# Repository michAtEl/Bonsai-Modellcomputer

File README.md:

# Bonsai-Modellcomputer
Der Bonsai-Modellcomputer wurde von Klaus Merkert für den Einsatz im Informatikunterricht entwickelt. Auf folgender Seite findet man unter anderem Schaltpläne und Platinenlayouts von Klaus Merkert zum Bau eines Bonsai-Modellcomputers:
http://www.hsg-kl.de/faecher/inf/material/bonsai/

Es gibt auch eine Simulation des Lerncomputers (https://bonsai.pinyto.de/), die im digitalen Informatik-Schulbuch http://inf-schule.de verwendet wird.

Viele Bauteile, die in den Plänen von Klaus Merkert verwendet werden, wurden abgekündigt und sind heue (Stand 2021) nicht mehr verfügbar.
Ziel dieses Projektes ist es deshalb, eine Version des Bonsai-Modellcomputer zu entwickeln, die möglichst leicht nachgebaut werden kann.

# Projekstatus
Der Prototyp funktioniert und wurde im Unterricht eingesetzt. In den Github-Issues sind einige kleinere Probleme beschrieben, die vor einem weiteren Nachbau behoben werden könnten.

# Änderungen gegenüber den Plänen von Klaus Merkert
- Die Namen und Reihenfolge der Steuersignale wurden an den Simulator angepasst (vgl. https://bonsai.pinyto.de/documentation/micro/)
- Alle Schaltpläne und Platinen wurden mit der Software KiCad gezeichnet (http://kicad.org).
- Für die Platinen wurden neue Layouts entwickelt, damit die Möglichkeiten eines doppelseitigen Layouts besser genutzt werden können.
- Die Steckverbinder zur Verbindung der Steuersignale sowie der Spannungsversorgung mit den Platinen wurden ersetzt durch Reichelt PSK (Alternativ kann man Molex KK verwenden. Diese Steckverbinder sind besser, aber auch deutlich teurer).
- Alle Bauteile der Familie 74LS wurden durch Bauteile der Familien 74HC oder 74HCT ersetzt.
- Zur Nullentdeckung auf der Platine Befehle wurde eine Wired-And-Verknüpfung mit Open-Collector-Ausgängen verwendet. Diese Wired-And-Verknüpfung wurde durch Gatter in einem 74HC08 ersetzt.
- Zur Erzeugung eines automatischen Taktsignals wird ein Mikrocontroller (Atmega 48-20P) verwendet. Der Quellcode liegt im Verzeichnis EinTaktReset-src. Der Quellcode kann mit dem Microchip Studio compiliert werden. Der Mikrocontroller kann anschließend über den ISP-Header auf der Platine EinTaktReset programmiert werden.

# Eine Bonsai nachbauen
## Beschaffung der Bauteile
- Flachbandkabel: Diese Flachbandkabel kann man aus IDE-Kabeln herstellen.
- Taster Digitast: Diese Schalter sind in den letzten Jahren sehr teuer geworden (ca. 5€ pro Taster). Kompatible Nachbauten findet man auf der Seite https://de.aliexpress.com/ unter der Bezeichnung PB86. Zur Sicherheit: Datenblatt (insbesondere Abmessungen und interne Schaltung) prüfen!
- Die Steckverbinder 

## Platinen fertigen lassen
Die Pläne wurden mit KiCad gezeichnet. In den *.kicad_sch-Dateien befinden sich die Schaltpläne, die Platinenlayouts sind in den *.kicad_pcb-Dateien. Um die Platinen fertigen zu lassen, muss man das Platinenlayout in ein Format exportieren, dass der Hersteller versteht. In der Regel ist das Gerber. Die Gerber-Exporte, die bei dem Prototypen verwendet wurden, liegen im Verzeichnis gerber. Diese Gerber-Dateien wurden von https://jlcpcb.com/ problemlos gefertigt.

## Platinen bestücken
Es werden nur bedrahtete Bauteile (keine SMD-Bauteile) verwendet, da bedrahtete Bauteile von Lötanfängern (z.B. Schülern) leichter bestückt werden können. Es ist sinnvoll, bei allen ICs je einen Sockel zu verwenden.

Der Bestückungsdruck der Platinen wird für Hinweise zur Bedienung des Rechners verwendet.
Die Bezeichnungen der Bauteile stehen nicht im Bestückungsdruck.
Man erfährt diese Bezeichnungen, indem man das KiCad-Projekt zu der Platinen, an der man gerade arbeitet, betrachtet. Dazu öffnet man zunächst die Projektdatei (.kicad_pro). Aus der Kicad-Projektansicht kann man dann den Schaltplan und das Board mit einem Doppelclick öffnen. Wenn man die Dateien so öffnet, sind Schaltplan und Board verknüpft. D.h.: Klickt man im Schaltplan / Board auf ein Bauteil, so wird dieses Bauteil automatisch auch im Bard / Schaltplan hervorgehoben. So versteht man leichter, welche Aufgabe ein bestimmtes Bauteil auf dem Board hat. 

Es empfiehlt sich, die Platinen in der folgenden Reihenfolge zu bestücken:
- Spanngsversorgung (KiCad-Projekt power-schmal). Diese Platine wird später benötigt, um andere Platinen zu testen.
- Akku und PC. Diese Platinen können einzeln getestet werden. Achtung: Die Platinen sind gleich, sie unterscheiden sich jedoch in der Farbe der LEDs und den Widerständen R2 und R2 (vgl. Schaltplan sowie [Bonsai.jpg](Bonsai.jpg))
- Speicher
- Ein/Takt/Reset. Nun können alle bisher gebauten Platinen gemeinsam getestet werden. Man verkabelt die Platinen. Dann kann man mit den Kippschaltern Zahlen eingeben, diese Zahlen speichern und anschließend wider auf den Datenbus schreiben.
- restliche Platinen

## Platine Ein/Takt/Reset
Von dieser Platine gibt es eine neue Version. Im Bild [Bonsai.jpg](Bonsai.jpg) ist noch die alte Version abgebildet. In der neuen Version wird der Takt von einem Mikrocontroller (ATmega48) erzeugt. Dieser Controller muss programmiert werden. Die Programmierung kann direkt in der Schaltung mit Hilfe der 6-poligen Pinleiste erfolgen. Man benötigt dazu einen ISP-Adapter für ATmega-Controller. Der Quellcode befindet sich im Ordner EinTaktReset-src.

## Platinen verdrahten
Bei der Verdrahtung kann man sich orientieren
- [am Bild des Computers](Bonsai.jpg)
- [Verdrahtung](Verdrahtung.svg) Tipp: Datei in Inkscape öffnen; die Datei ist im Maßstab 1:1 gezeichnet
- an der Verdrahtungsanleitung von Klaus Merkert (https://www.hsg-kl.de/faecher/inf/material/bonsai/bau/verdraht/index.php)

Crimpanleitung für die Steckverbinder Reichelt PSK: https://www.reichelt.de/reicheltpedia/index.php/Crimp_Anleitungen#Crimpen_von_PSK-Kontakten

Als Flachbandkabel kann man alte IDE-Kabel verwenden. Mann muss jedoch einige Leitungen abtrennen und neue Stecker crimpen.

Die Kabelhalter können mit einem 3D-Drucker gedruckt werden. Eine OpenSCAD-Datei befindet sich im Ordner Kabelhalter: [Kabelhalter.scad](Kabelhalter/Kabelhalter.scad)

## Spannungsversorgung
Der Bonsai läuft mit einer Gleichspannung von 5V. Es mehrere Möglichkeiten, wie man diese Spannung bereitstellen kann:

- Man verwendet ein Festspannungsnetzteil, das 5V ausgibt. Aus Lochrasterplatinenmaterial baut man eine Platine, auf der sich eine Buchse für das Netzteil sowie sechs 2-polige Steckerleisten für 2-polige PSK-Stecker befinden (pro Platine eine Steckerleiste).
- Man baut eine kleine Platine mit einem Festspannungsregler (7805). Dazu kann man z.B. die Platine im Ordner power-schmal verwenden. Diese Platine benötigt eine Eingangsspannung, die irgendwo zwischen ca. 7V und ca. 15V liegen sollte. Dazu kann man z.B. ein Labornetzgerät verwenden.  Das Labornetzgerät hat gegenüber einem Steckernetzteil den Vorteil, dass man die Stromstärke an dem Netzteil ablesen kann und so eine kontrolle hat, ob der Bonsai richtig funktioniert. Bei dem vollständigen Bonsai liegt die Stromstärke (je nach dem, wie viele LEDs gerade leuchten und welche Vorwiderstände für die LEDs verwendet wurden) bei ca. 50mA - 300mA.

## Helligkeit der LEDs
Die Leds sind sehr hell. Bei einem Nachbau könnte man größere Vorwiderstände verwenden. Nach der Anschaffung der LEDs könnte man die Helligkeit einer LED bei verschiedenen Vorwiderständen ausprobieren (Led in Reihe schalten mit Vorwiderstand) und dann festlegen, welchen Vorwiderstand man verwendet.

Bei LEDs, die von einem Pin eines 74HCXX getrieben werden, sollte der Vorwiderstand mindestens 600Ohm betragen, wenn man innerhalb der Empfehlungen von TI bleiben möchte (vgl. Issue #5). Dies gilt jedoch nicht für LEDs, die von einem 74HC540 oder 74HC541 getrieben werden, da diese beiden ICs Leistungstreiber sind.

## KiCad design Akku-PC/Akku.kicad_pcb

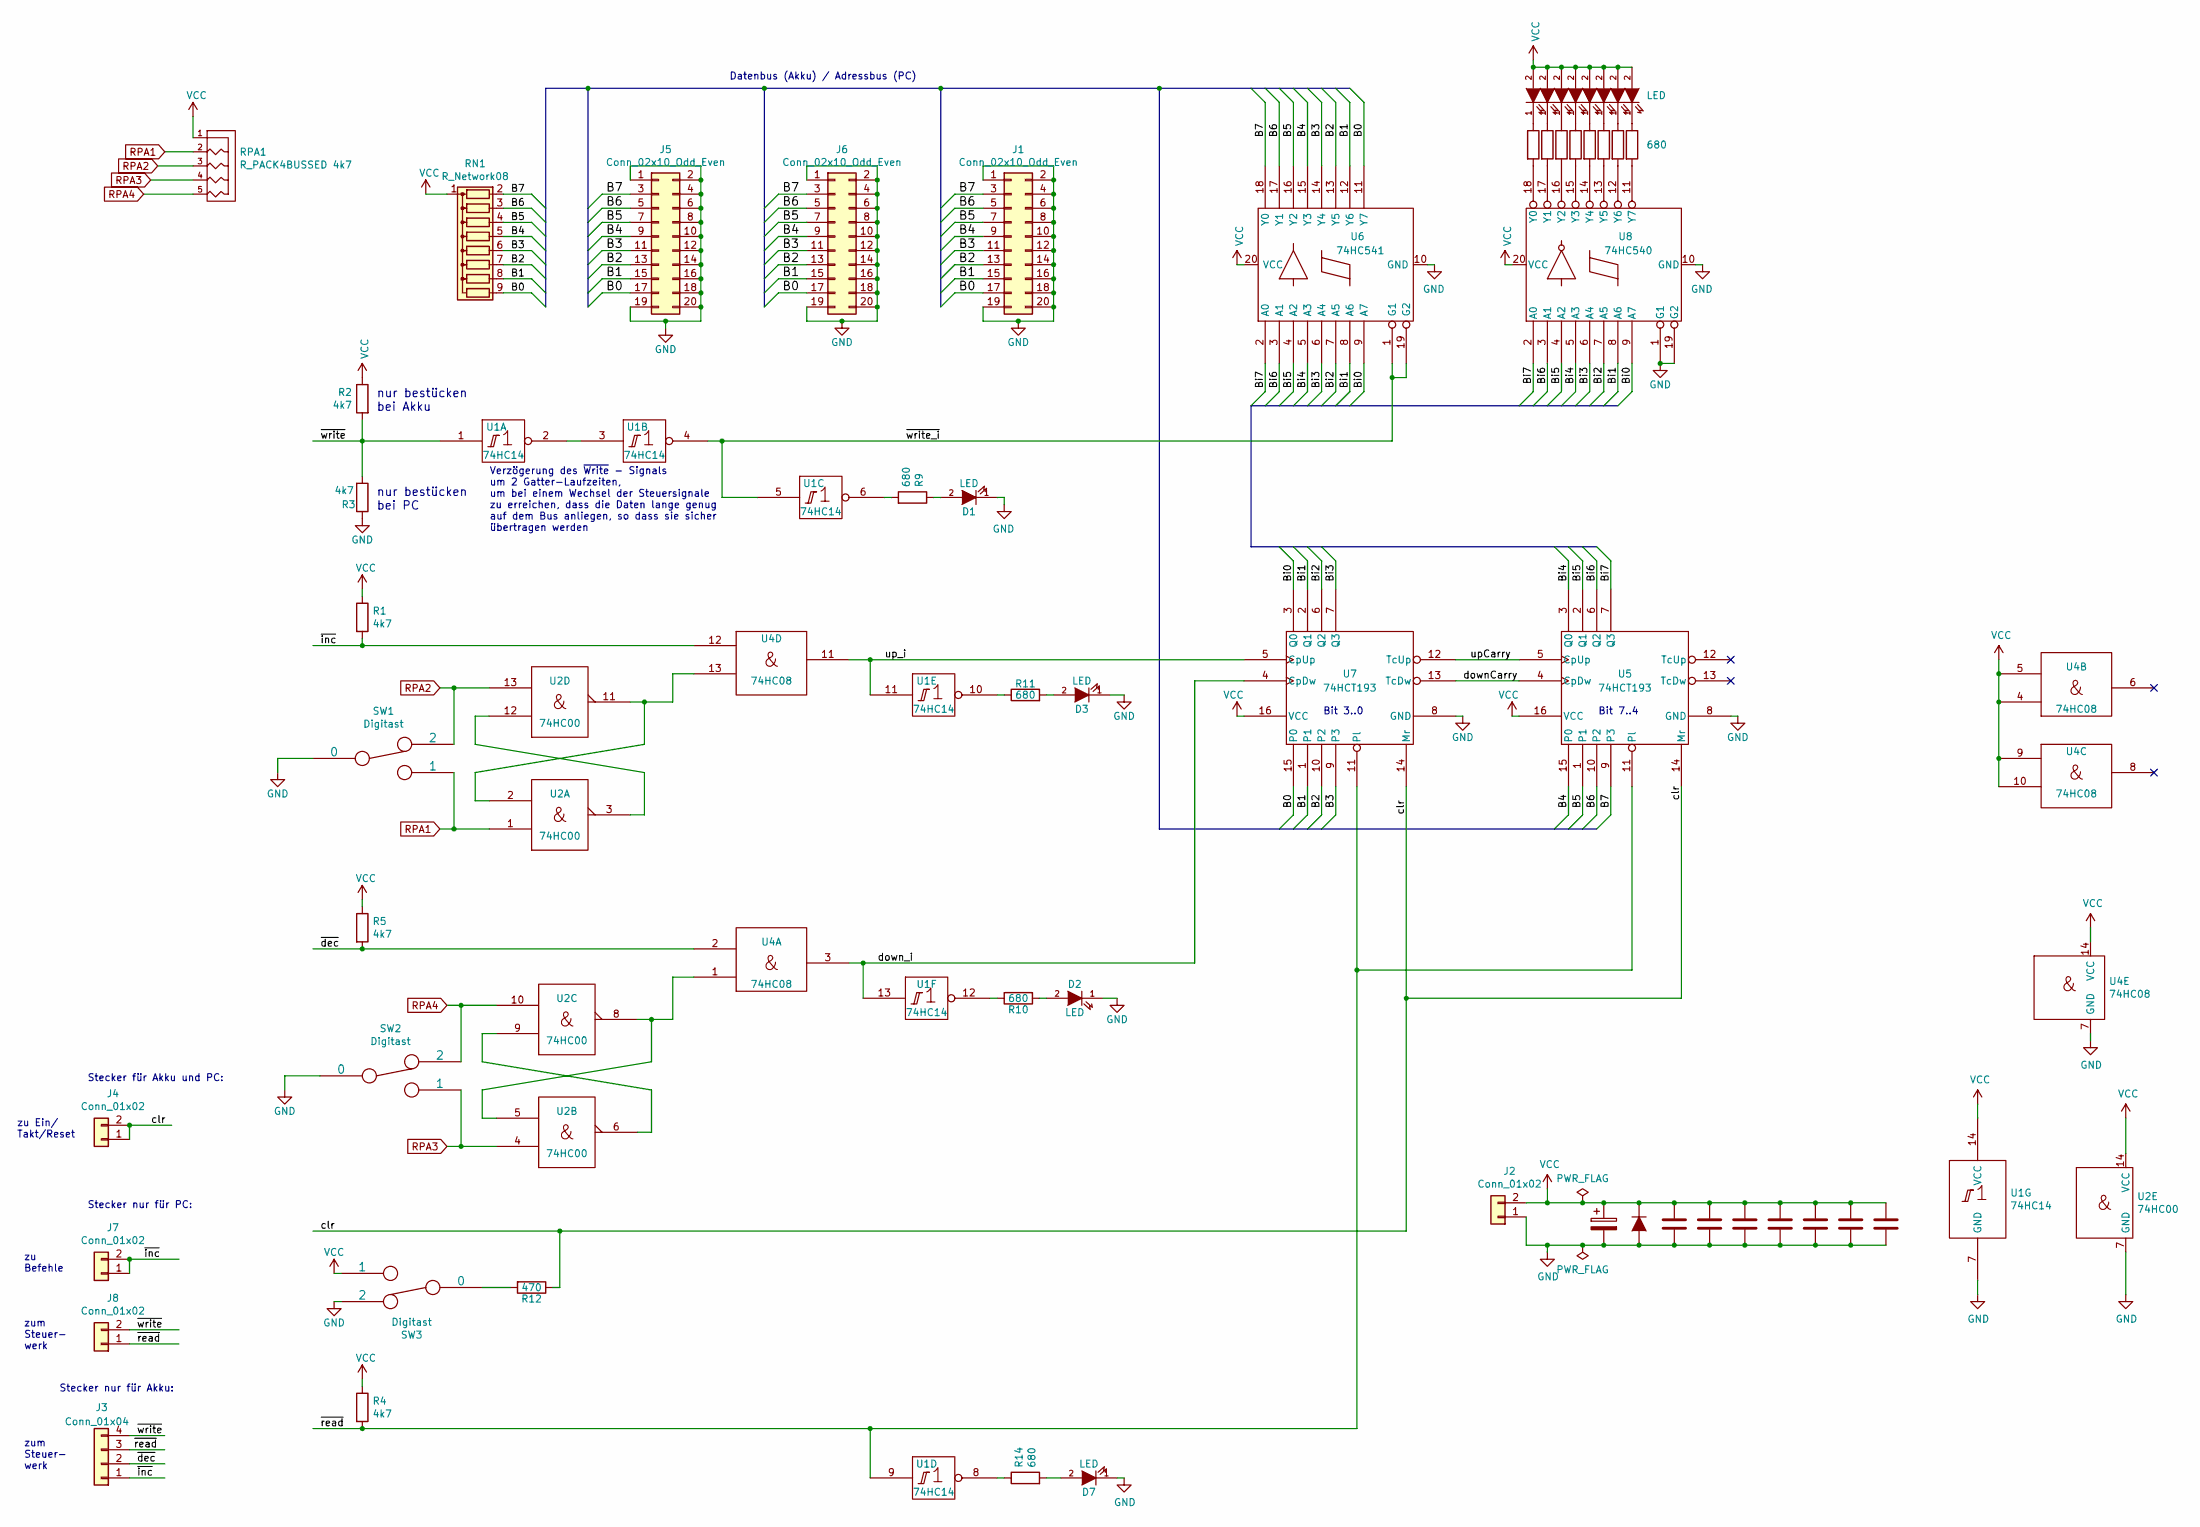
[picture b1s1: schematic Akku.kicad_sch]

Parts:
C1, C2, C3, C5, C6, C7, C8: 100n; C_Disc_D10.0mm_W2.5mm_P5.00mm
C4: CP; CP_Radial_D8.0mm_P2.50mm
D1, D2, D3, D4, D5, D6, D7, D8, D9, D10, D11, D12: LED; LED_D3.0mm
D13: D; D_A-405_P10.16mm_Horizontal
J1, J5, J6: Conn_02x10_Odd_Even; PinHeader_2x10_P2.54mm_Vertical
J2, J4, J7, J8: Conn_01x02; Molex_KK-254_AE-6410-02A_1x02_P2.54mm_Vertical
J3: Conn_01x04; Molex_KK-254_AE-6410-04A_1x04_P2.54mm_Vertical
R1, R2, R3, R4, R5: 4k7; R_Axial_DIN0207_L6.3mm_D2.5mm_P10.16mm_Horizontal
R9, R10, R11, R13, R14, R15, R16, R17, R18, R19, R20, R21: 680; R_Axial_DIN0207_L6.3mm_D2.5mm_P10.16mm_Horizontal
R12: 470; R_Axial_DIN0207_L6.3mm_D2.5mm_P10.16mm_Horizontal
RN1: R_Network08; R_Array_SIP9
RPA1: R_PACK4BUSSED 4k7; R_Array_SIP5
SW1, SW2, SW3: Digitast; Switch_Digitast
U1: 74HC14; DIP-14_W7.62mm_Socket_LongPads
U2: 74HC00; DIP-14_W7.62mm_Socket_LongPads
U4: 74HC08; DIP-14_W7.62mm_Socket_LongPads
U5, U7: 74HCT193; DIP-16_W7.62mm_Socket_LongPads
U6: 74HC541; DIP-20_W7.62mm_Socket_LongPads
U8: 74HC540; DIP-20_W7.62mm_Socket_LongPads

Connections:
/B0: J1.17, J5.17, J6.17, RN1.9 (R8), U6.11 (Y7), U7.15 (P0)
/B1: J1.15, J5.15, J6.15, RN1.8 (R7), U6.12 (Y6), U7.1
/B2: J1.13, J5.13, J6.13, RN1.7 (R6), U6.13 (Y5), U7.10 (P2)
/B3: J1.11, J5.11, J6.11, RN1.6 (R5), U6.14 (Y4), U7.9 (P3)
/B4: J1.9, J5.9, J6.9, RN1.5 (R4), U5.15 (P0), U6.15 (Y3)
/B5: J1.7, J5.7, J6.7, RN1.4 (R3), U5.1, U6.16 (Y2)
/B6: J1.5, J5.5, J6.5, RN1.3 (R2), U5.10 (P2), U6.17 (Y1)
/B7: J1.3, J5.3, J6.3, RN1.2 (R1), U5.9 (P3), U6.18 (Y0)
/Bi0: U6.9 (A7), U7.3 (Q0), U8.9 (A7)
/Bi1: U6.8 (A6), U7.2 (Q1), U8.8 (A6)
/Bi2: U6.7 (A5), U7.6 (Q2), U8.7 (A5)
/Bi3: U6.6 (A4), U7.7 (Q3), U8.6 (A4)
/Bi4: U5.3 (Q0), U6.5 (A3), U8.5 (A3)
/Bi5: U5.2 (Q1), U6.4 (A2), U8.4 (A2)
/Bi6: U5.6 (Q2), U6.3 (A1), U8.3 (A1)
/Bi7: U5.7 (Q3), U6.2 (A0), U8.2 (A0)
/clr: J4.1, J4.2, R12.1, U5.14 (Mr), U7.14 (Mr)
/downCarry: U5.4 (CpDw), U7.13 (TcDw)
/down_i: U1.13, U4.3, U7.4 (CpDw)
/upCarry: U5.5 (CpUp), U7.12 (TcUp)
/up_i: U1.11, U4.11, U7.5 (CpUp)
/~dec: J3.2, R5.2, U4.2
/~inc: J3.1, J7.1, J7.2, R1.2, U4.12
/~read: J3.3, J8.1, R4.2, U1.9, U5.11 (Pl), U7.11 (Pl)
/~write_i: U1.4, U1.5, U6.1 (G1), U6.19 (G2)
/~write: J3.4, J8.2, R2.2, R3.2, U1.1
GND: C1.1, C2.1, C3.1, C4.2, C5.1, C6.1, C7.1, C8.1, D1.1 (K), D2.1 (K), D3.1 (K), D7.1 (K), D13.2 (A), J1.1, J1.2, J1.4, J1.6, J1.8, J1.10, J1.12, J1.14, J1.16, J1.18, J1.19, J1.20, J2.1, J5.1, J5.2, J5.4, J5.6, J5.8, J5.10, J5.12, J5.14, J5.16, J5.18, J5.19, J5.20, J6.1, J6.2, J6.4, J6.6, J6.8, J6.10, J6.12, J6.14, J6.16, J6.18, J6.19, J6.20, R3.1, SW1.0, SW2.0, SW3.2, U1.7 (GND), U2.7 (GND), U4.7 (GND), U5.8 (GND), U6.10 (GND), U7.8 (GND), U8.1 (G1), U8.10 (GND), U8.19 (G2)
unnamed: D1.2 (A), R9.1
unnamed: D2.2 (A), R10.2
unnamed: D3.2 (A), R11.2
unnamed: D4.1 (K), R13.1
unnamed: D5.1 (K), R15.1
unnamed: D6.1 (K), R16.1
unnamed: D7.2 (A), R14.2
unnamed: D8.1 (K), R17.1
unnamed: D9.1 (K), R18.1
unnamed: D10.1 (K), R19.1
unnamed: D11.1 (K), R20.1
unnamed: D12.1 (K), R21.1
unnamed: R9.2, U1.6
unnamed: R10.1, U1.12
unnamed: R11.1, U1.10
unnamed: R12.2, SW3.0
unnamed: R14.1, U1.8
unnamed: U1.2, U1.3
unnamed: U2.5, U2.8, U4.1
unnamed: U2.6, U2.9
unnamed: U2.2, U2.11, U4.13
unnamed: U2.3, U2.12
unnamed: R13.2, U8.18 (Y0)
unnamed: R15.2, U8.17 (Y1)
unnamed: R16.2, U8.16 (Y2)
unnamed: R17.2, U8.15 (Y3)
unnamed: R18.2, U8.14 (Y4)
unnamed: R19.2, U8.13 (Y5)
unnamed: R20.2, U8.12 (Y6)
unnamed: R21.2, U8.11 (Y7)
RPA1: RPA1.2, SW1.1, U2.1
RPA2: RPA1.3, SW1.2, U2.13
RPA3: RPA1.4, SW2.1, U2.4
RPA4: RPA1.5, SW2.2, U2.10
VCC: C1.2, C2.2, C3.2, C4.1, C5.2, C6.2, C7.2, C8.2, D4.2 (A), D5.2 (A), D6.2 (A), D8.2 (A), D9.2 (A), D10.2 (A), D11.2 (A), D12.2 (A), D13.1 (K), J2.2, R1.1, R2.1, R4.1, R5.1, RN1.1 (common), RPA1.1, SW3.1, U1.14 (VCC), U2.14 (VCC), U4.4, U4.5, U4.9, U4.10, U4.14 (VCC), U5.16 (VCC), U6.20 (VCC), U7.16 (VCC), U8.20 (VCC)

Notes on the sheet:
zum Steuer- werk
Stecker für Akku und PC:
Bit 7..4
nur bestücken bei Akku
zu Ein/ Takt/Reset
Stecker nur für PC:
nur bestücken bei PC
Datenbus (Akku) / Adressbus (PC)
Bit 3..0
Verzögerung des ~{Write} - Signals um 2 Gatter-Laufzeiten, um bei einem Wechsel der Steuersignale zu erreichen, dass die Daten lange genug auf dem Bus anliegen, so dass sie sicher übertragen werden
zu Befehle
Stecker nur für Akku:

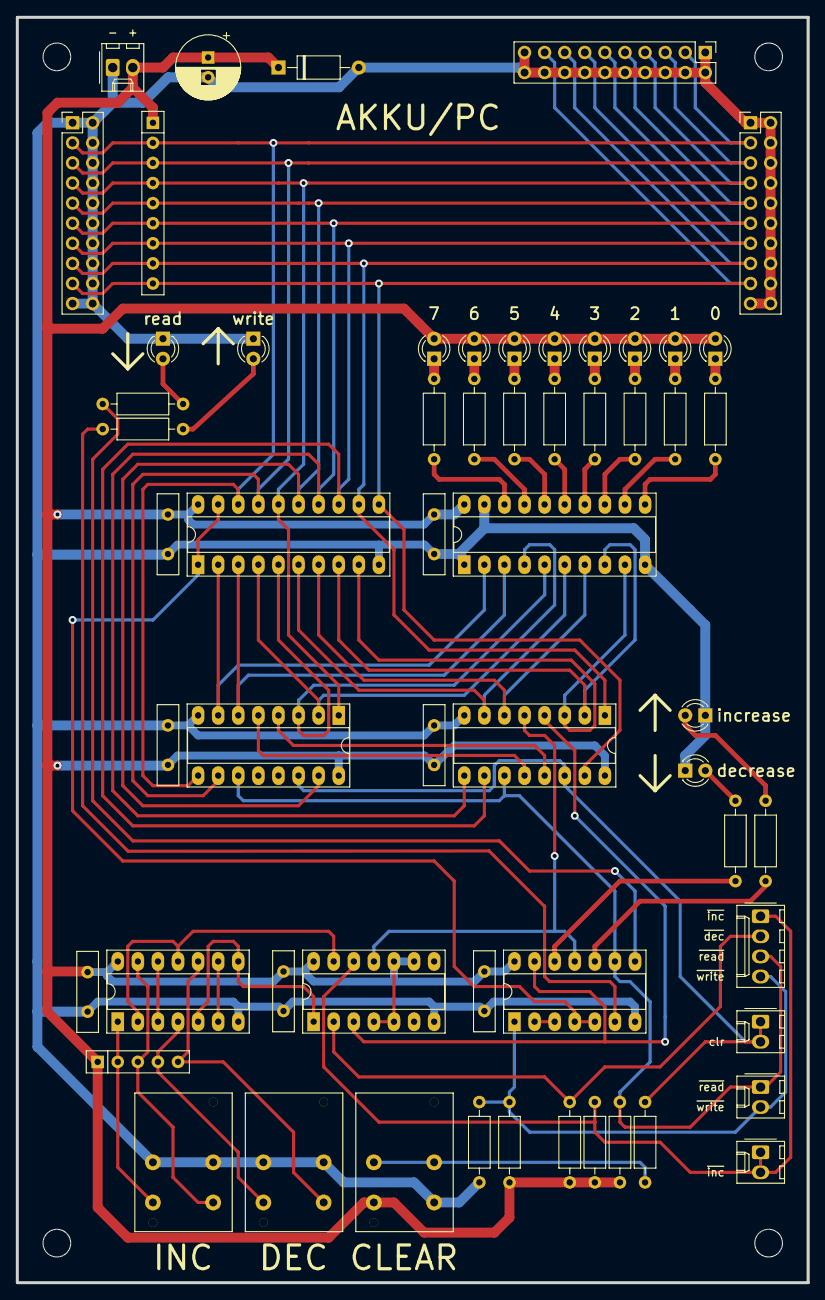
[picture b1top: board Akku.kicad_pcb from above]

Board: 2 copper layers, 100.0 x 160.0 mm, 59 parts (0 on the bottom side), 62 nets.

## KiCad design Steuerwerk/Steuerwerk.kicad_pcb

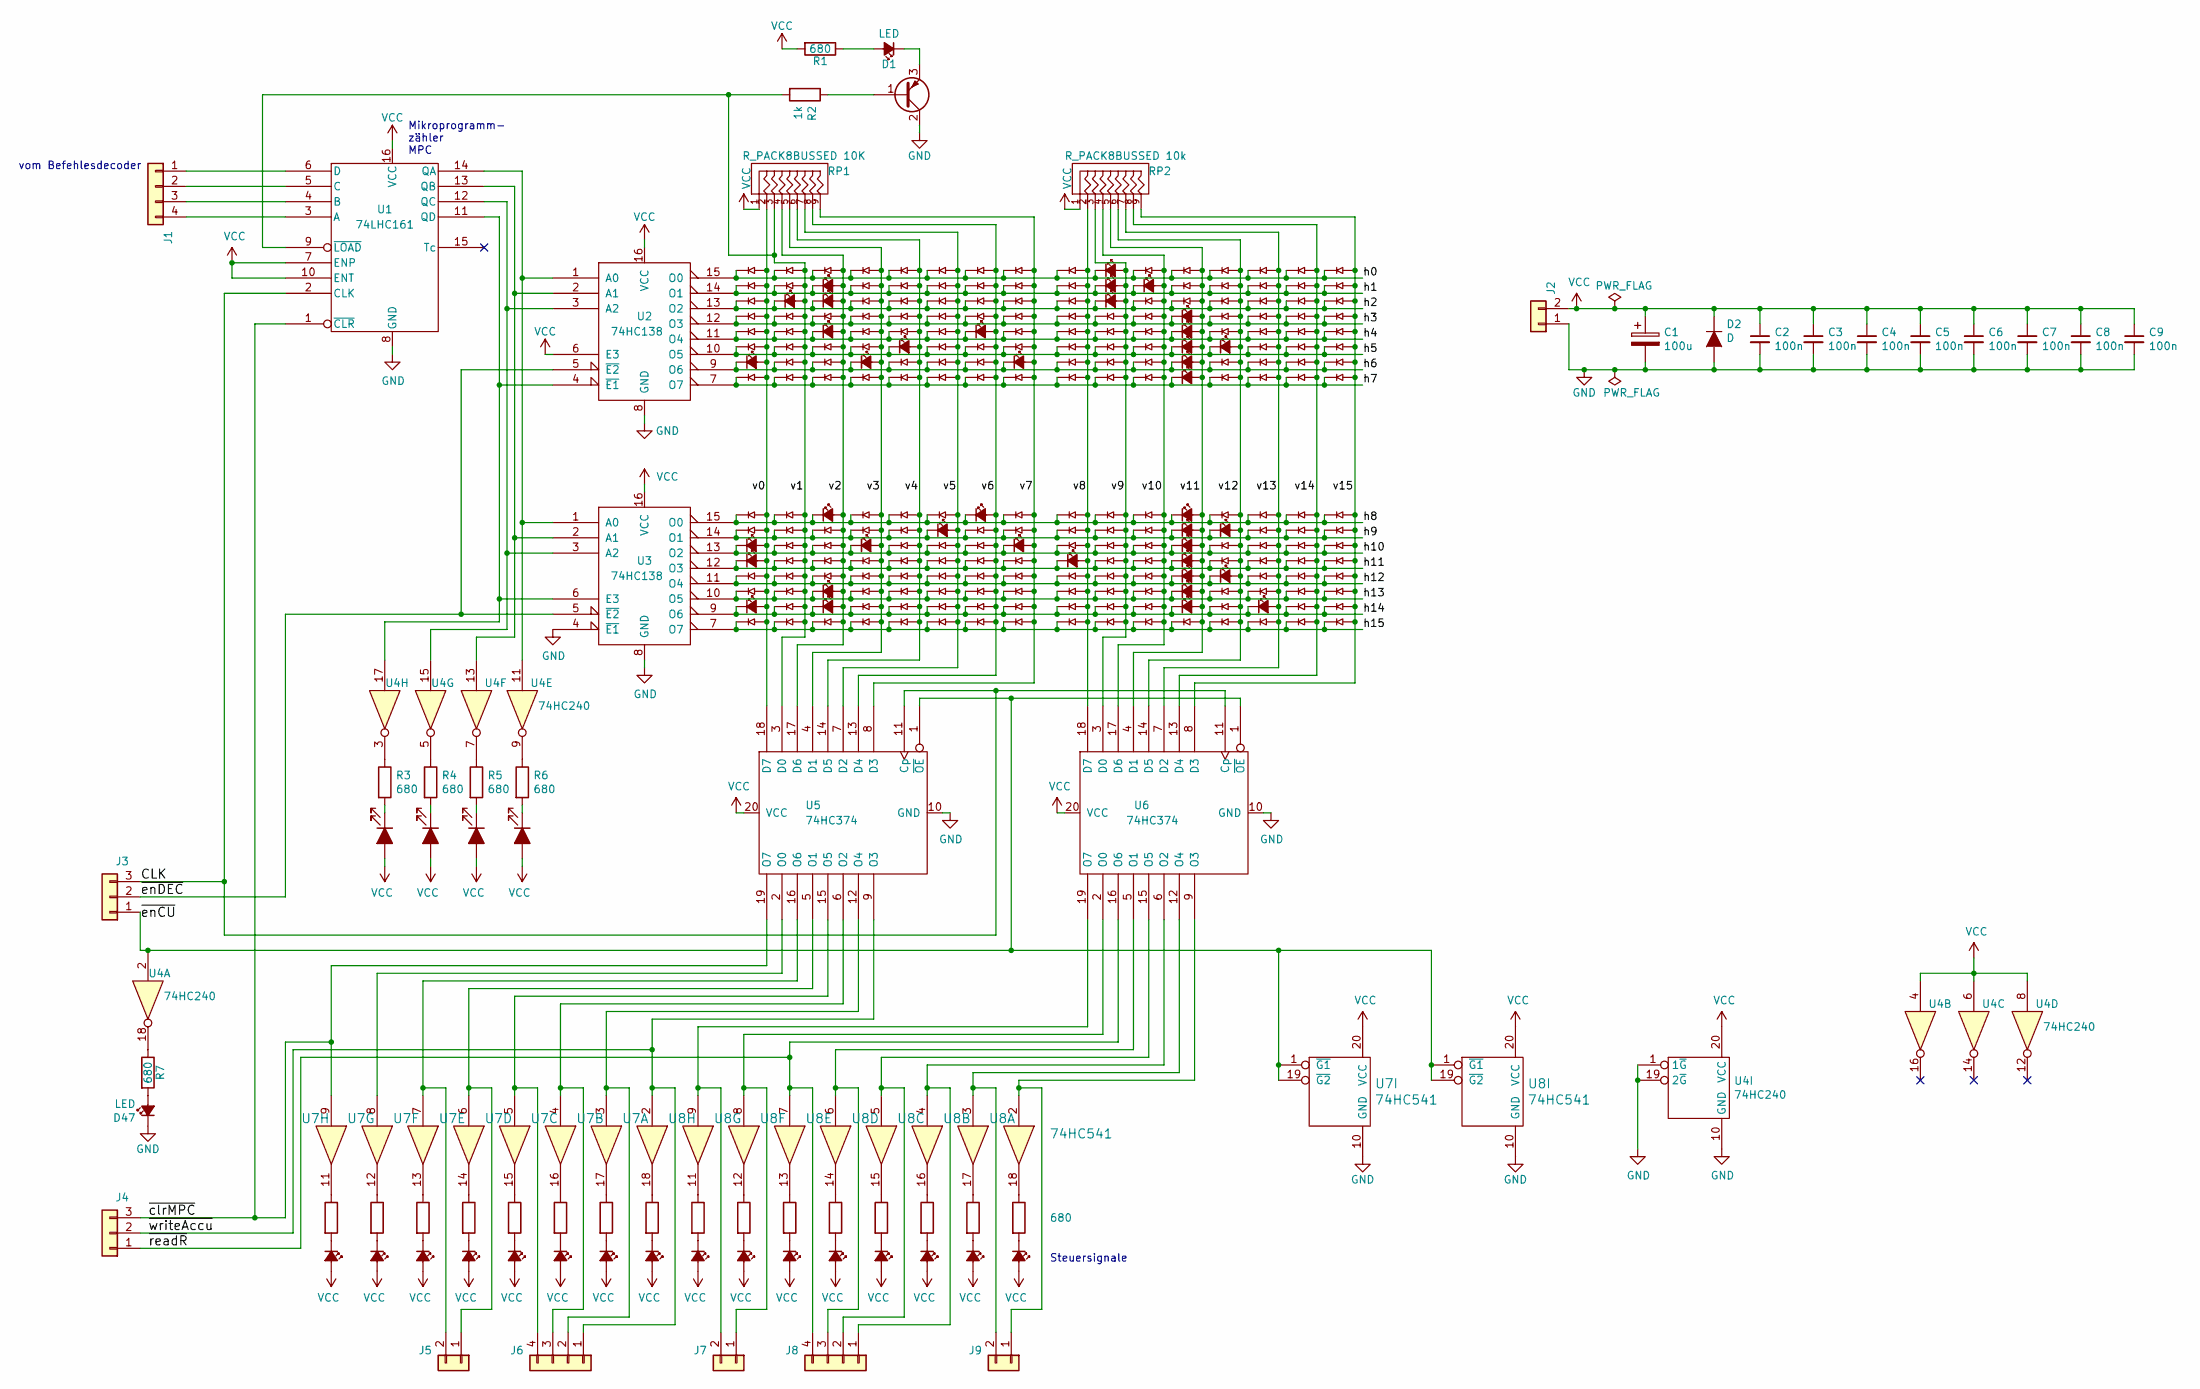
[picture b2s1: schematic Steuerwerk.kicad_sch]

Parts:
C1: 100u; CP_Radial_D8.0mm_P2.50mm
C2, C3, C4, C5, C6, C7, C8, C9: 100n; C_Disc_D10.0mm_W2.5mm_P5.00mm
D1, D43, D44, D45, D46, D47, D48, D49, D50, D51, D52, D53, D54, D55, D56, D57, D58, D59, D60, D61, D62, D63: LED; LED_D3.0mm
D2: D; D_A-405_P10.16mm_Horizontal
D3, D4, D5, D6, D7, D8, D9, D10, D11, D12, D13, D14, D15, D16, D17, D18, D19, D20, D21, D22, D23, D24, D25, D26, D27, D28, D29, D30, D31, D32, D33, D34, D35, D36, D37, D38, D39, D40, D41, D42: Led_Small; LED_Diodenmatrix
D64, D65, D66, D67, D68, D69, D70, D71, D72, D73, D74, D75, D76, D77, D78, D79, D80, D81, D82, D83, D84, D85, D86, D87, D88, D89, D90, D91, D92, D93, D94, D95, D96, D97, D98, D99, D100, D101, D102, D103, D104, D105, D106, D107, D108, D109, D110, D111, D112, D113, D114, D115, D116, D117, D118, D119, D120, D121, D122, D123, D124, D125, D126, D127, D128, D129, D130, D131, D132, D133, D134, D135, D136, D137, D138, D139, D140, D141, D142, D143, D144, D145, D146, D147, D148, D149, D150, D151, D152, D153, D154, D155, D156, D157, D158, D159, D160, D161, D162, D163, D164, D165, D166, D167, D168, D169, D170, D171, D172, D173, D174, D175, D176, D177, D178, D179, D180, D181, D182, D183, D184, D185, D186, D187, D188, D189, D190, D191, D192, D193, D194, D195, D196, D197, D198, D199, D200, D201, D202, D203, D204, D205, D206, D207, D208, D209, D210, D211, D212, D213, D214, D215, D216, D217, D218, D219, D220, D221, D222, D223, D224, D225, D226, D227, D228, D229, D230, D231, D232, D233, D234, D235, D236, D237, D238, D239, D240, D241, D242, D243, D244, D245, D246, D247, D248, D249, D250, D251, D252, D253, D254, D255, D256, D257, D258, D259, D260, D261, D262, D263, D264, D265, D266, D267, D268, D269, D270, D271, D272, D273, D274, D275, D276, D277, D278, D279: bonsai_Led_Small_Platzhalter; LED_Diodenmatrix_Platzhalter
J1, J6, J8: Conn_01x04; Molex_KK-254_AE-6410-04A_1x04_P2.54mm_Vertical
J2, J5, J7, J9: Conn_01x02; Molex_KK-254_AE-6410-02A_1x02_P2.54mm_Vertical
J3, J4: Conn_01x03; Molex_KK-254_AE-6410-03A_1x03_P2.54mm_Vertical
Q1: Q_PNP_BCE; TO-92_Inline_Wide
R1, R3, R4, R5, R6, R7, R8, R9, R10, R11, R12, R13, R14, R15, R16, R17, R18, R19, R20, R21, R22, R23: 680; R_Axial_DIN0207_L6.3mm_D2.5mm_P10.16mm_Horizontal
R2: 1k; R_Axial_DIN0207_L6.3mm_D2.5mm_P10.16mm_Horizontal
RP1: R_PACK8BUSSED 10K; SIP9_Housing_BigPads
RP2: R_PACK8BUSSED 10k; SIP9_Housing_BigPads
U1: 74LHC161; DIP-16_W7.62mm_Socket_LongPads
U2, U3: 74HC138; DIP-16_W7.62mm_Socket_LongPads
U4: 74HC240; DIP-20_W7.62mm_Socket_LongPads
U5, U6: 74HC374; DIP-20_W7.62mm_Socket_LongPads
U7, U8: 74HC541; DIP-20_W7.62mm_Socket_LongPads

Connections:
/CLK: J3.3, U1.2 (CLK), U5.11 (Cp), U6.11 (Cp)
/h0: D4.1 (K), D64.1 (K), D65.1 (K), D66.1 (K), D67.1 (K), D68.1 (K), D69.1 (K), D70.1 (K), D71.1 (K), D173.1 (K), D174.1 (K), D175.1 (K), D176.1 (K), D177.1 (K), D178.1 (K), D179.1 (K), U2.15 (O0)
/h1: D3.1 (K), D5.1 (K), D6.1 (K), D72.1 (K), D73.1 (K), D74.1 (K), D75.1 (K), D76.1 (K), D77.1 (K), D78.1 (K), D180.1 (K), D181.1 (K), D182.1 (K), D183.1 (K), D184.1 (K), D185.1 (K), U2.14 (O1)
/h2: D7.1 (K), D8.1 (K), D9.1 (K), D79.1 (K), D80.1 (K), D81.1 (K), D82.1 (K), D83.1 (K), D84.1 (K), D186.1 (K), D187.1 (K), D188.1 (K), D189.1 (K), D190.1 (K), D191.1 (K), D192.1 (K), U2.13 (O2)
/h3: D11.1 (K), D85.1 (K), D86.1 (K), D87.1 (K), D88.1 (K), D89.1 (K), D90.1 (K), D91.1 (K), D92.1 (K), D193.1 (K), D205.1 (K), D218.1 (K), D232.1 (K), D242.1 (K), D254.1 (K), D255.1 (K), U2.12 (O3)
/h4: D12.1 (K), D13.1 (K), D14.1 (K), D93.1 (K), D94.1 (K), D95.1 (K), D96.1 (K), D97.1 (K), D98.1 (K), D194.1 (K), D206.1 (K), D219.1 (K), D233.1 (K), D243.1 (K), D256.1 (K), D257.1 (K), U2.11 (O4)
/h5: D15.1 (K), D16.1 (K), D17.1 (K), D99.1 (K), D100.1 (K), D101.1 (K), D102.1 (K), D103.1 (K), D104.1 (K), D105.1 (K), D195.1 (K), D207.1 (K), D220.1 (K), D244.1 (K), D258.1 (K), D259.1 (K), U2.10 (O5)
/h6: D10.1 (K), D18.1 (K), D19.1 (K), D20.1 (K), D106.1 (K), D107.1 (K), D108.1 (K), D109.1 (K), D110.1 (K), D196.1 (K), D208.1 (K), D221.1 (K), D234.1 (K), D245.1 (K), D260.1 (K), D261.1 (K), U2.9 (O6)
/h7: D21.1 (K), D111.1 (K), D112.1 (K), D113.1 (K), D114.1 (K), D115.1 (K), D116.1 (K), D117.1 (K), D118.1 (K), D197.1 (K), D209.1 (K), D222.1 (K), D235.1 (K), D246.1 (K), D262.1 (K), D263.1 (K), U2.7 (O7)
/h8: D22.1 (K), D23.1 (K), D24.1 (K), D119.1 (K), D120.1 (K), D121.1 (K), D122.1 (K), D123.1 (K), D124.1 (K), D198.1 (K), D210.1 (K), D223.1 (K), D236.1 (K), D247.1 (K), D264.1 (K), D265.1 (K), U3.15 (O0)
/h9: D25.1 (K), D26.1 (K), D27.1 (K), D125.1 (K), D126.1 (K), D127.1 (K), D128.1 (K), D129.1 (K), D130.1 (K), D131.1 (K), D199.1 (K), D211.1 (K), D224.1 (K), D248.1 (K), D266.1 (K), D267.1 (K), U3.14 (O1)
/h10: D28.1 (K), D29.1 (K), D30.1 (K), D31.1 (K), D132.1 (K), D133.1 (K), D134.1 (K), D135.1 (K), D136.1 (K), D200.1 (K), D212.1 (K), D225.1 (K), D237.1 (K), D249.1 (K), D268.1 (K), D269.1 (K), U3.13 (O2)
/h11: D32.1 (K), D33.1 (K), D34.1 (K), D137.1 (K), D138.1 (K), D139.1 (K), D140.1 (K), D141.1 (K), D142.1 (K), D143.1 (K), D213.1 (K), D226.1 (K), D238.1 (K), D250.1 (K), D270.1 (K), D271.1 (K), U3.12 (O3)
/h12: D35.1 (K), D36.1 (K), D144.1 (K), D145.1 (K), D146.1 (K), D147.1 (K), D148.1 (K), D149.1 (K), D150.1 (K), D151.1 (K), D201.1 (K), D214.1 (K), D227.1 (K), D251.1 (K), D272.1 (K), D273.1 (K), U3.11 (O4)
/h13: D37.1 (K), D38.1 (K), D152.1 (K), D153.1 (K), D154.1 (K), D155.1 (K), D156.1 (K), D157.1 (K), D158.1 (K), D202.1 (K), D215.1 (K), D228.1 (K), D239.1 (K), D252.1 (K), D274.1 (K), D275.1 (K), U3.10 (O5)
/h14: D39.1 (K), D40.1 (K), D41.1 (K), D42.1 (K), D159.1 (K), D160.1 (K), D161.1 (K), D162.1 (K), D163.1 (K), D164.1 (K), D203.1 (K), D216.1 (K), D229.1 (K), D240.1 (K), D276.1 (K), D277.1 (K), U3.9 (O6)
/h15: D165.1 (K), D166.1 (K), D167.1 (K), D168.1 (K), D169.1 (K), D170.1 (K), D171.1 (K), D172.1 (K), D204.1 (K), D217.1 (K), D230.1 (K), D231.1 (K), D241.1 (K), D253.1 (K), D278.1 (K), D279.1 (K), U3.7 (O7)
/~clrMPC: J4.3, U1.1 (~CLR), U5.19 (O7), U7.9
/~enCU: J3.1, U4.2, U5.1 (~OE), U6.1 (~OE), U7.1 (~G1), U7.19 (~G2), U8.1 (~G1), U8.19 (~G2)
/~enDEC: J3.2, U2.5 (~E2), U3.5 (~E2)
/~readR: J4.1, J8.4, U6.16 (O6), U8.7
/~writeAccu: J4.2, J6.1, U5.9 (O3), U7.2
GND: C1.2, C2.2, C3.2, C4.2, C5.2, C6.2, C7.2, C8.2, C9.2, D2.2 (A), D47.1 (K), J2.1, Q1.2 (C), U1.8 (GND), U2.8 (GND), U3.4 (~E1), U3.8 (GND), U4.1 (1~G), U4.10 (GND), U4.19 (2~G), U5.10 (GND), U6.10 (GND), U7.10 (GND), U8.10 (GND)
unnamed: D1.2 (A), R1.1
unnamed: D1.1 (K), Q1.3 (E)
unnamed: D10.2 (A), D28.2 (A), D32.2 (A), D39.2 (A), D64.2 (A), D72.2 (A), D79.2 (A), D85.2 (A), D93.2 (A), D99.2 (A), D111.2 (A), D119.2 (A), D125.2 (A), D144.2 (A), D152.2 (A), D165.2 (A), RP1.2, U5.18 (D7)
unnamed: D11.2 (A), D14.2 (A), D16.2 (A), D20.2 (A), D21.2 (A), D24.2 (A), D26.2 (A), D31.2 (A), D34.2 (A), D35.2 (A), D38.2 (A), D41.2 (A), D175.2 (A), D181.2 (A), D188.2 (A), D231.2 (A), RP2.5, U6.4 (D1)
unnamed: D17.2 (A), D27.2 (A), D36.2 (A), D176.2 (A), D182.2 (A), D189.2 (A), D232.2 (A), D233.2 (A), D234.2 (A), D235.2 (A), D236.2 (A), D237.2 (A), D238.2 (A), D239.2 (A), D240.2 (A), D241.2 (A), RP2.6, U6.14 (D5)
unnamed: D43.1 (K), R3.2
unnamed: D44.1 (K), R4.2
unnamed: D45.1 (K), R5.2
unnamed: D46.1 (K), R6.2
unnamed: D47.2 (A), R7.2
unnamed: D48.1 (K), R8.2
unnamed: D49.1 (K), R9.2
unnamed: D50.1 (K), R10.2
unnamed: D51.1 (K), R11.2
unnamed: D52.1 (K), R12.2
unnamed: D53.1 (K), R13.2
unnamed: D54.1 (K), R14.2
unnamed: D55.1 (K), R15.2
unnamed: D56.1 (K), R16.2
unnamed: D57.1 (K), R17.2
unnamed: D58.1 (K), R18.2
unnamed: D59.1 (K), R19.2
unnamed: D60.1 (K), R20.2
unnamed: D61.1 (K), R21.2
unnamed: D62.1 (K), R22.2
unnamed: D63.1 (K), R23.2
unnamed: D7.2 (A), D65.2 (A), D73.2 (A), D86.2 (A), D94.2 (A), D100.2 (A), D106.2 (A), D112.2 (A), D120.2 (A), D126.2 (A), D132.2 (A), D137.2 (A), D145.2 (A), D153.2 (A), D159.2 (A), D166.2 (A), R2.2, RP1.3, U1.9 (~LOAD), U5.3 (D0)
unnamed: D3.2 (A), D8.2 (A), D12.2 (A), D22.2 (A), D37.2 (A), D40.2 (A), D66.2 (A), D87.2 (A), D101.2 (A), D107.2 (A), D113.2 (A), D127.2 (A), D133.2 (A), D138.2 (A), D146.2 (A), D167.2 (A), RP1.4, U5.17 (D6)
unnamed: D18.2 (A), D29.2 (A), D67.2 (A), D74.2 (A), D80.2 (A), D88.2 (A), D95.2 (A), D102.2 (A), D114.2 (A), D121.2 (A), D128.2 (A), D139.2 (A), D147.2 (A), D154.2 (A), D160.2 (A), D168.2 (A), RP1.5, U5.4 (D1)
unnamed: D25.2 (A), D69.2 (A), D76.2 (A), D82.2 (A), D90.2 (A), D97.2 (A), D103.2 (A), D109.2 (A), D116.2 (A), D123.2 (A), D135.2 (A), D141.2 (A), D149.2 (A), D156.2 (A), D162.2 (A), D170.2 (A), RP1.7, U5.7 (D2)
unnamed: D13.2 (A), D23.2 (A), D70.2 (A), D77.2 (A), D83.2 (A), D91.2 (A), D104.2 (A), D110.2 (A), D117.2 (A), D130.2 (A), D136.2 (A), D142.2 (A), D150.2 (A), D157.2 (A), D163.2 (A), D171.2 (A), RP1.8, U5.13 (D4)
unnamed: D19.2 (A), D30.2 (A), D71.2 (A), D78.2 (A), D84.2 (A), D92.2 (A), D98.2 (A), D105.2 (A), D118.2 (A), D124.2 (A), D131.2 (A), D143.2 (A), D151.2 (A), D158.2 (A), D164.2 (A), D172.2 (A), RP1.9, U5.8 (D3)
unnamed: D15.2 (A), D68.2 (A), D75.2 (A), D81.2 (A), D89.2 (A), D96.2 (A), D108.2 (A), D115.2 (A), D122.2 (A), D129.2 (A), D134.2 (A), D140.2 (A), D148.2 (A), D155.2 (A), D161.2 (A), D169.2 (A), RP1.6, U5.14 (D5)
unnamed: D33.2 (A), D173.2 (A), D180.2 (A), D186.2 (A), D193.2 (A), D194.2 (A), D195.2 (A), D196.2 (A), D197.2 (A), D198.2 (A), D199.2 (A), D200.2 (A), D201.2 (A), D202.2 (A), D203.2 (A), D204.2 (A), RP2.2, U6.18 (D7)
unnamed: D6.2 (A), D174.2 (A), D187.2 (A), D218.2 (A), D219.2 (A), D220.2 (A), D221.2 (A), D222.2 (A), D223.2 (A), D224.2 (A), D225.2 (A), D226.2 (A), D227.2 (A), D228.2 (A), D229.2 (A), D230.2 (A), RP2.4, U6.17 (D6)
unnamed: D42.2 (A), D177.2 (A), D183.2 (A), D190.2 (A), D242.2 (A), D243.2 (A), D244.2 (A), D245.2 (A), D246.2 (A), D247.2 (A), D248.2 (A), D249.2 (A), D250.2 (A), D251.2 (A), D252.2 (A), D253.2 (A), RP2.7, U6.7 (D2)
unnamed: D178.2 (A), D184.2 (A), D191.2 (A), D254.2 (A), D256.2 (A), D258.2 (A), D260.2 (A), D262.2 (A), D264.2 (A), D266.2 (A), D268.2 (A), D270.2 (A), D272.2 (A), D274.2 (A), D276.2 (A), D278.2 (A), RP2.8, U6.13 (D4)
unnamed: D179.2 (A), D185.2 (A), D192.2 (A), D255.2 (A), D257.2 (A), D259.2 (A), D261.2 (A), D263.2 (A), D265.2 (A), D267.2 (A), D269.2 (A), D271.2 (A), D273.2 (A), D275.2 (A), D277.2 (A), D279.2 (A), RP2.9, U6.8 (D3)
unnamed: D4.2 (A), D5.2 (A), D9.2 (A), D205.2 (A), D206.2 (A), D207.2 (A), D208.2 (A), D209.2 (A), D210.2 (A), D211.2 (A), D212.2 (A), D213.2 (A), D214.2 (A), D215.2 (A), D216.2 (A), D217.2 (A), RP2.3, U6.3 (D0)
unnamed: J1.1, U1.6 (D)
unnamed: J1.2, U1.5 (C)
unnamed: J1.3, U1.4 (B)
unnamed: J1.4, U1.3 (A)
unnamed: J5.1, U5.5 (O1), U7.6
unnamed: J5.2, U5.16 (O6), U7.7
unnamed: J6.2, U5.12 (O4), U7.3
unnamed: J6.3, U5.6 (O2), U7.4
unnamed: J6.4, U5.15 (O5), U7.5
unnamed: J7.1, U6.2 (O0), U8.8
unnamed: J7.2, U6.19 (O7), U8.9
unnamed: J8.1, U6.6 (O2), U8.4
unnamed: J8.2, U6.15 (O5), U8.5
unnamed: J8.3, U6.5 (O1), U8.6
unnamed: J9.1, U6.9 (O3), U8.2
unnamed: J9.2, U6.12 (O4), U8.3
unnamed: Q1.1 (B), R2.1
unnamed: R3.1, U4.3
unnamed: R4.1, U4.5
unnamed: R5.1, U4.7
unnamed: R6.1, U4.9
unnamed: R7.1, U4.18
unnamed: R8.1, U7.11
unnamed: R9.1, U7.12
unnamed: R10.1, U7.13
unnamed: R11.1, U7.14
unnamed: R12.1, U7.15
unnamed: R13.1, U7.16
unnamed: R14.1, U7.17
unnamed: R15.1, U7.18
unnamed: R16.1, U8.11
unnamed: R17.1, U8.12
unnamed: R18.1, U8.13
unnamed: R19.1, U8.14
unnamed: R20.1, U8.15
unnamed: R21.1, U8.16
unnamed: R22.1, U8.17
unnamed: R23.1, U8.18
unnamed: U1.14 (QA), U2.1 (A0), U3.1 (A0), U4.11
unnamed: U1.13 (QB), U2.2 (A1), U3.2 (A1), U4.13
unnamed: U1.12 (QC), U2.3 (A2), U3.3 (A2), U4.15
unnamed: U1.11 (QD), U2.4 (~E1), U3.6 (E3), U4.17
unnamed: U5.2 (O0), U7.8
VCC: C1.1, C2.1, C3.1, C4.1, C5.1, C6.1, C7.1, C8.1, C9.1, D2.1 (K), D43.2 (A), D44.2 (A), D45.2 (A), D46.2 (A), D48.2 (A), D49.2 (A), D50.2 (A), D51.2 (A), D52.2 (A), D53.2 (A), D54.2 (A), D55.2 (A), D56.2 (A), D57.2 (A), D58.2 (A), D59.2 (A), D60.2 (A), D61.2 (A), D62.2 (A), D63.2 (A), J2.2, R1.2, RP1.1, RP2.1, U1.7 (ENP), U1.10 (ENT), U1.16 (VCC), U2.6 (E3), U2.16 (VCC), U3.16 (VCC), U4.4, U4.6, U4.8, U4.20 (VCC), U5.20 (VCC), U6.20 (VCC), U7.20 (VCC), U8.20 (VCC)

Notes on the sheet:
Steuersignale
vom Befehlesdecoder
Mikroprogramm- zähler MPC

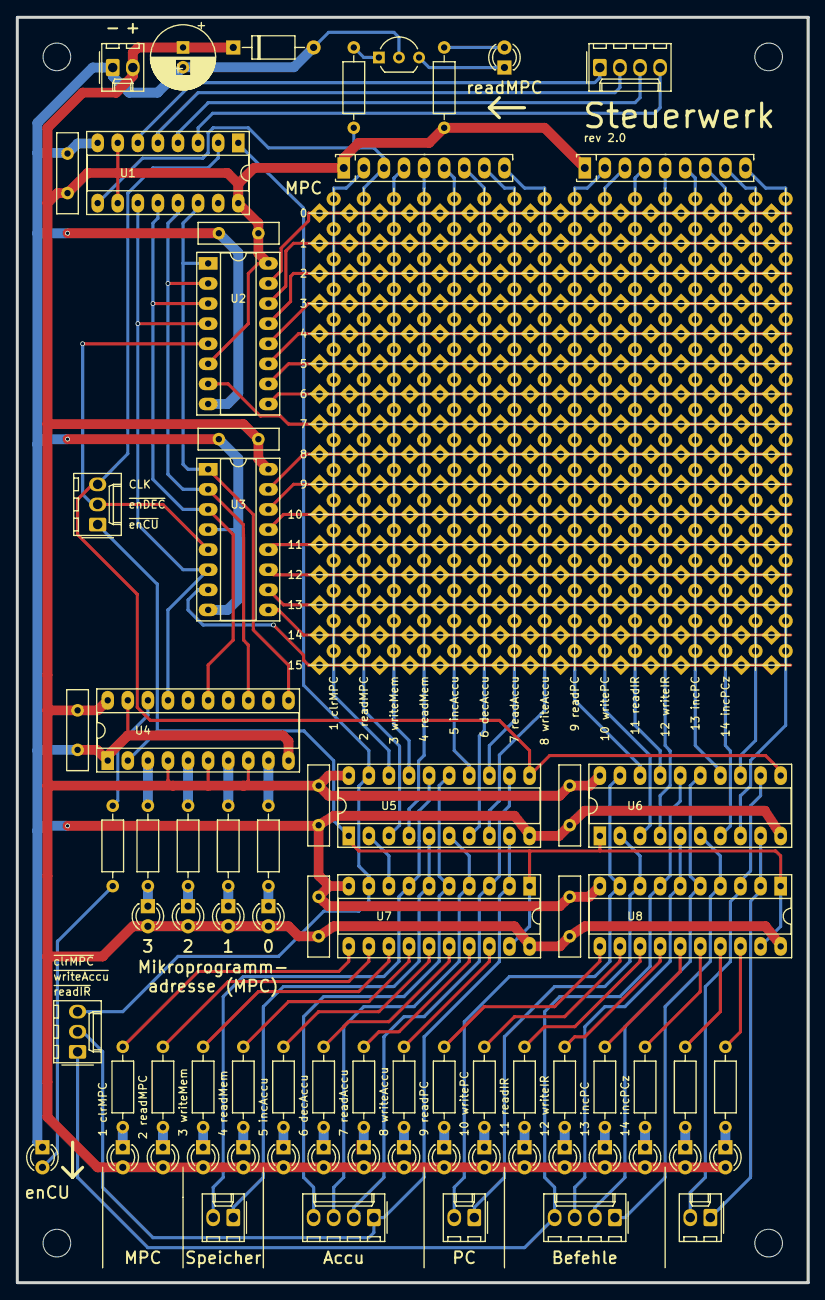
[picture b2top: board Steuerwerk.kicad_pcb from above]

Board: 2 copper layers, 100.0 x 160.0 mm, 331 parts (0 on the bottom side), 106 nets.
